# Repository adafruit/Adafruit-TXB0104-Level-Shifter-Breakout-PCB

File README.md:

## Adafruit TXB0104 Level Shifter Breakout PCB
<a href="http://www.adafruit.com/products/1875"><br/>
Click here to purchase one from the Adafruit shop</a>

This is lovely chip: the TXB0104 bi-directional level converter! This chip perform bidirectional level shifting from pretty much any voltage to any voltage and will auto-detect the direction. Only thing that doesn't work well with this chip is i2c (because it uses strong pullups which confuse auto-direction sensor) or control lines with a lot of capacitance on them. If you need to use pullups, you can but they should be at least 50K ohm - the ones internal to AVRs/Arduino are about 100K ohm so those are OK! Its a little more luxurious than a 74LVX245 but if you just don't want to worry about directional pins this is a life saver!

Since this chip is a special bi-directional level shifter it does not have strong output pins that can drive LEDs or long cables, it's meant to sit on a breadboard between two logic chips! If you do not need instant bi-directional support, we suggest the 74LVX245 as below which has stronger output drive.

PCB files for the Adafruit TXB0104 Level Shifter Breakout. The format is EagleCAD schematic and board layout
- https://www.adafruit.com/product/1875

### License

Adafruit invests time and resources providing this open source design, please support Adafruit and open-source hardware by purchasing products from [Adafruit](https://www.adafruit.com)!

All text above must be included in any redistribution

Designed by Limor Fried/Ladyada for Adafruit Industries.
Creative Commons Attribution/Share-Alike, all text above must be included in any redistribution. 
See license.txt for additional information.

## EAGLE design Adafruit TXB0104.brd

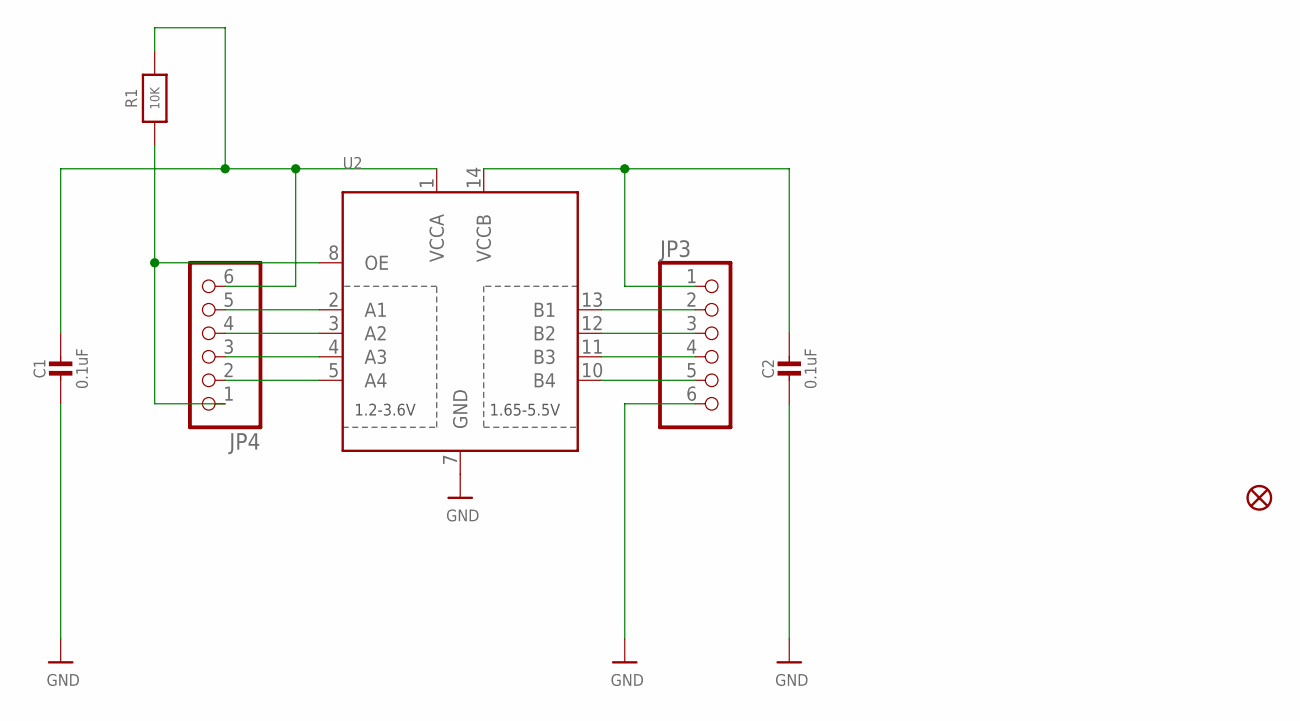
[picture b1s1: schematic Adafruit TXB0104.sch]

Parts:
C1, C2: 0.1uF; 0805-NO
JP3, JP4: PINHD-1X6CB; 1X06-CLEANBIG
R1: 10K; 0805-NO
U2: TXB0104PWR; TSSOP14
U$5: FIDUCIAL_1MM

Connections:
A1: JP4.5, U2.2 (A1)
A2: JP4.4, U2.3 (A2)
A3: JP4.3, U2.4 (A3)
A4: JP4.2, U2.5 (A4)
B1: JP3.2, U2.13 (B1)
B2: JP3.3, U2.12 (B2)
B3: JP3.4, U2.11 (B3)
B4: JP3.5, U2.10 (B4)
GND: C1.2, C2.2, JP3.6, U2.7 (GND)
OE: JP4.1, R1.1, U2.8 (OE)
VHIGH: C2.1, JP3.1, U2.14 (VCCB)
VLOW: C1.1, JP4.6, R1.2, U2.1 (VCCA)

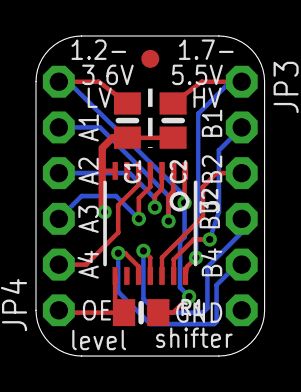
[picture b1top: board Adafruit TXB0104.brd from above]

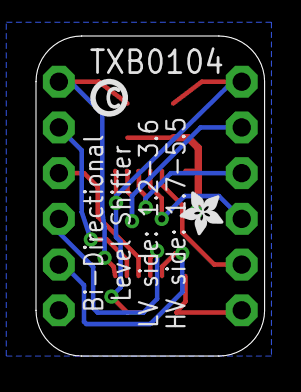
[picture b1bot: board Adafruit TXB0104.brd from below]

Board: 2 copper layers, 12.7 x 17.8 mm, 9 parts (2 on the bottom side), 12 nets.

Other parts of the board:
U$4: ADAFRUIT_2.5MM
U$7: PCBFEAT-REV-040

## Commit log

2016-08-25 init
2020-07-08 Remove previous version.
2020-07-08 Add updated board files.
